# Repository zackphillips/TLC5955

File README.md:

# Arduino Library for the TLC5955 LED controller
This library is designed to work with the TLC5955 LED controller chip from Texas Instruments.
It can also be configured to work with many other LED driver chips from the TLC59** family
using the #define values in the header file. Tested on the Teensy 3.2. The library currently calls Teensy-specific
APIs (`SPI.setMOSI`, `analogWriteFrequency`, `analogWriteResolution`), so other boards need those calls ported.
It supports all features of the TLC5955 datasheet such as:
- Per-LED color control and dimming (16-bit)
- Per-LED white-balance
- Support for many, many LEDs by daisy-chaining TLC5955 chips in hardware (up to 255, configurable by the `chip_count` static variable)
- Per color-channel current controller
- PWM spread spectrum (ESPWM flag)
- Optional total-current limit (`enforce_max_current` / `max_current_amps`), estimated from GS, DC, BC and MC per datasheet Equation 1 (`get_total_current()`)

# Installation
After downloading the [Arduino IDE](http://www.arduino.cc/), open `examples/TLC5955/TLC5955.ino` for an example of how to implement this class in your own sketch. Please note that static variables (`chip_count`, `max_current_amps`, `enforce_max_current`, and the `_dc_data`, `_rgb_order`, `_grayscale_data` arrays) must be defined in your sketch so the buffers are sized at compile time.

## Grayscale Clock (GSCLK)
This library works best with a LED clock pulse with a frequency of 1MHz or higher. Most micro-controllers can achieve this, but implementations may be different. For the Teensy, the built-in command ```analogWriteFrequency``` can reliably set the output frequency of a PIN. For other boards, a simple google search should show you which registers to set.

# Stability
This library is stable and well-tested using a Teensy 3.2, but may have bugs for other boards. Please file issues on Github if you find a bug. The API may change slightly as new features are added.

# Contributing
Contributions are encouraged! Please create a pull request on Github, file an issue, or send me a message on Github.

# License
BSD

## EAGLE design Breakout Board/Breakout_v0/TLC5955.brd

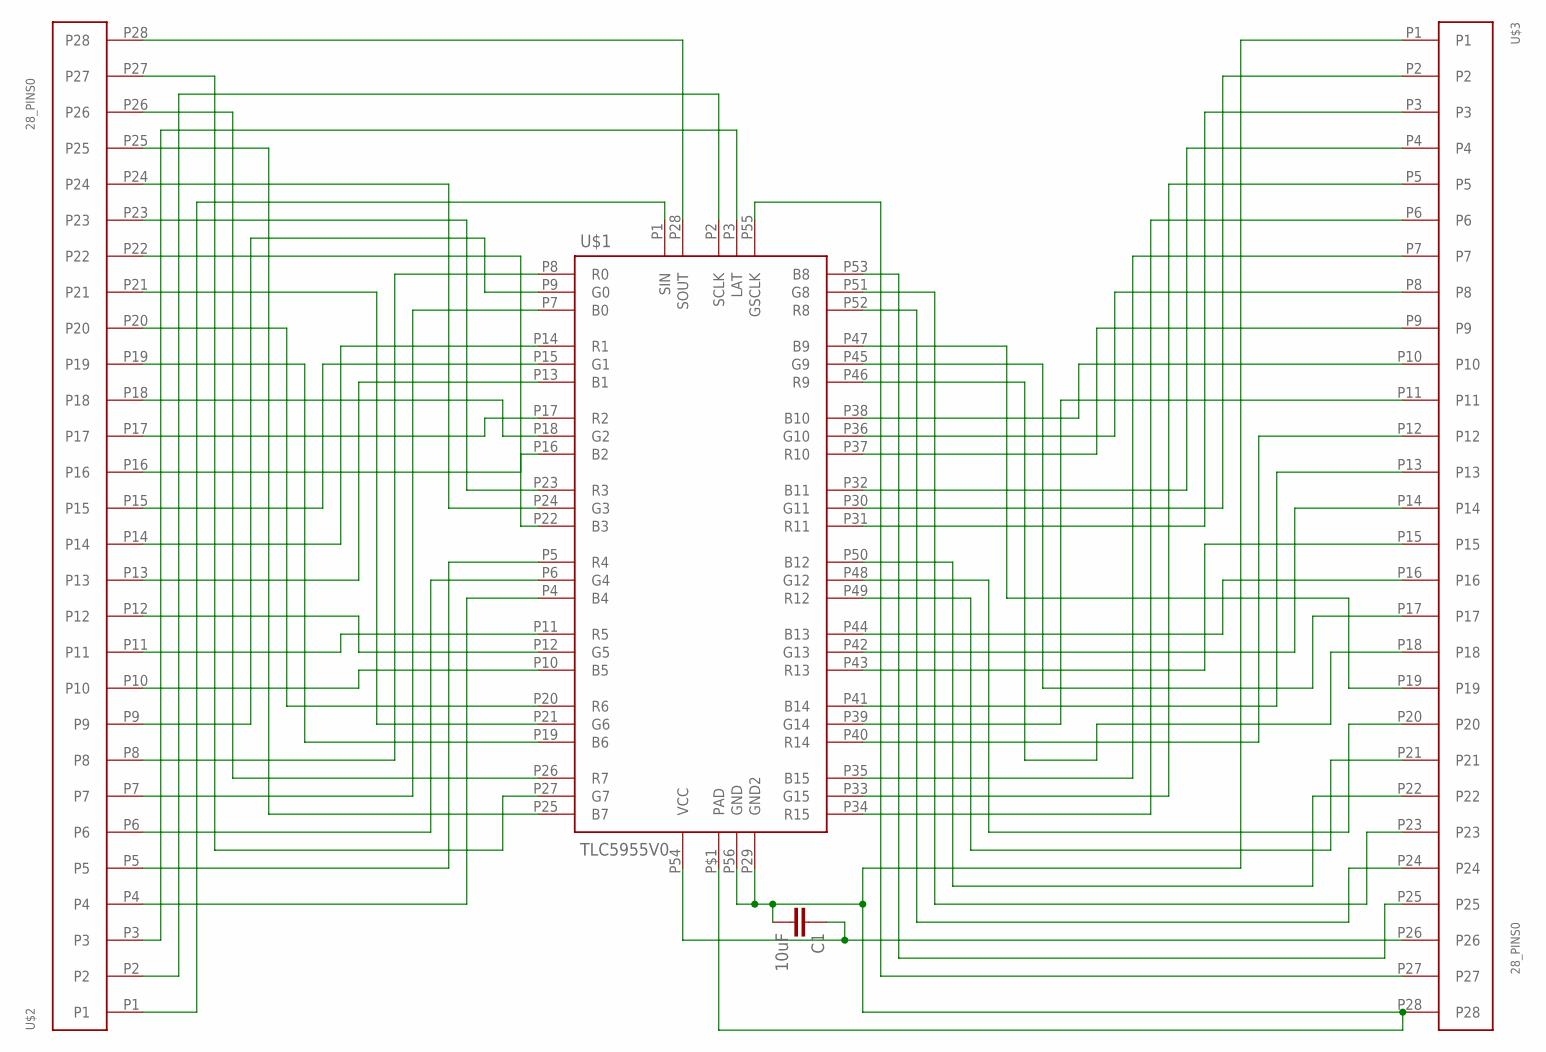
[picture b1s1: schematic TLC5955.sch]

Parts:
C1: 10uF; 0603-CAP
U$1: TLC5955V0; 56-HTSSOP
U$2, U$3: 28_PINS0; 28PIN_HOLES

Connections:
unnamed: U$1.P4 (B4), U$2.P4
unnamed: U$1.P5 (R4), U$2.P5
unnamed: U$1.P6 (G4), U$2.P6
unnamed: U$1.P7 (B0), U$2.P7
unnamed: U$1.P8 (R0), U$2.P8
unnamed: U$1.P21 (G6), U$2.P21
unnamed: U$1.P10 (B5), U$2.P10
unnamed: U$1.P11 (R5), U$2.P11
unnamed: U$1.P12 (G5), U$2.P12
unnamed: U$1.P13 (B1), U$2.P13
unnamed: U$1.P14 (R1), U$2.P14
unnamed: U$1.P15 (G1), U$2.P15
unnamed: U$1.P16 (B2), U$2.P16
unnamed: U$1.P17 (R2), U$2.P17
unnamed: U$1.P18 (G2), U$2.P18
unnamed: U$1.P19 (B6), U$2.P19
unnamed: U$1.P20 (R6), U$2.P20
unnamed: U$1.P22 (B3), U$2.P22
unnamed: U$1.P23 (R3), U$2.P23
unnamed: U$1.P24 (G3), U$2.P24
unnamed: U$1.P9 (G0), U$2.P9
unnamed: U$1.P25 (B7), U$2.P25
unnamed: U$1.P26 (R7), U$2.P26
unnamed: U$1.P28 (SOUT), U$2.P28
unnamed: U$1.P27 (G7), U$2.P27
unnamed: U$1.P1 (SIN), U$2.P1
unnamed: U$1.P2 (SCLK), U$2.P2
unnamed: U$1.P3 (LAT), U$2.P3
unnamed: U$1.P47 (B9), U$3.P19
unnamed: C1.1, U$1.P54 (VCC), U$3.P26
unnamed: U$1.P30 (G11), U$3.P2
unnamed: U$1.P31 (R11), U$3.P3
unnamed: U$1.P32 (B11), U$3.P4
unnamed: U$1.P33 (G15), U$3.P5
unnamed: U$1.P34 (R15), U$3.P6
unnamed: U$1.P35 (B15), U$3.P7
unnamed: U$1.P36 (G10), U$3.P8
unnamed: U$1.P37 (R10), U$3.P9
unnamed: U$1.P38 (B10), U$3.P10
unnamed: U$1.P39 (G14), U$3.P11
unnamed: U$1.P40 (R14), U$3.P12
unnamed: U$1.P41 (B14), U$3.P13
unnamed: U$1.P42 (G13), U$3.P14
unnamed: U$1.P43 (R13), U$3.P15
unnamed: U$1.P44 (B13), U$3.P16
unnamed: U$1.P45 (G9), U$3.P17
unnamed: U$1.P46 (R9), U$3.P18
unnamed: U$1.P48 (G12), U$3.P20
unnamed: U$1.P49 (R12), U$3.P21
unnamed: U$1.P50 (B12), U$3.P22
unnamed: U$1.P51 (G8), U$3.P23
unnamed: U$1.P52 (R8), U$3.P24
unnamed: U$1.P53 (B8), U$3.P25
unnamed: U$1.P55 (GSCLK), U$3.P27
unnamed: C1.2, U$1.P29 (GND2), U$1.P56 (GND), U$1.P$1 (PAD), U$3.P1, U$3.P28

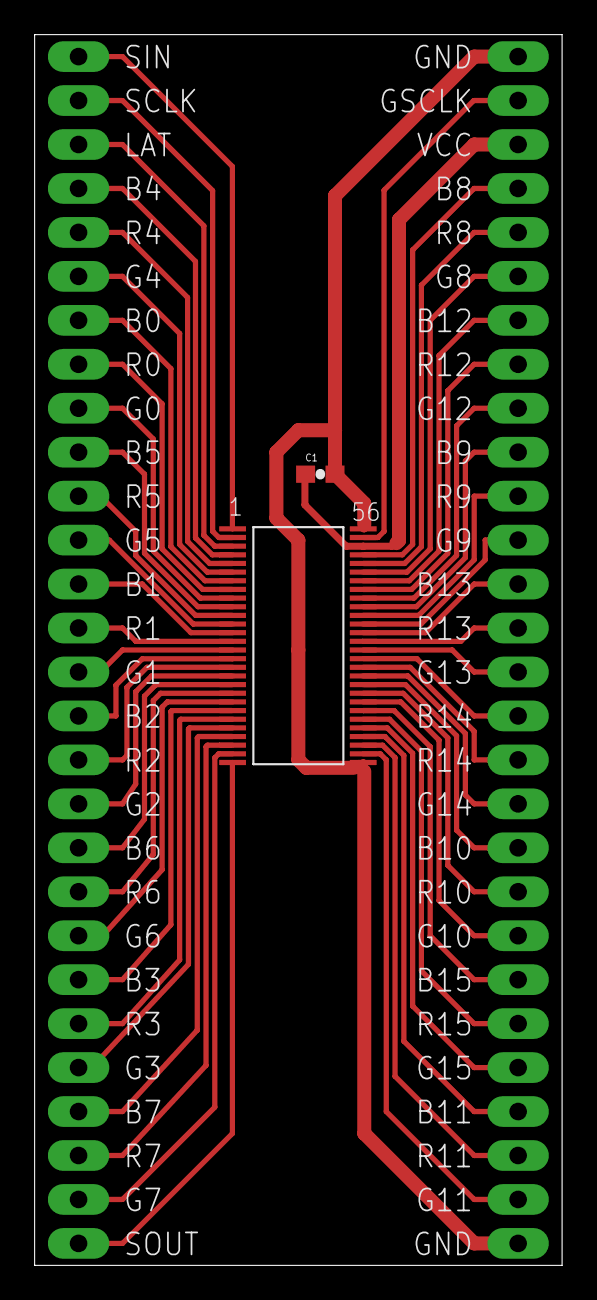
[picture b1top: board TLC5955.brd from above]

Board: 2 copper layers, 30.5 x 71.1 mm, 4 parts (0 on the bottom side), 55 nets.

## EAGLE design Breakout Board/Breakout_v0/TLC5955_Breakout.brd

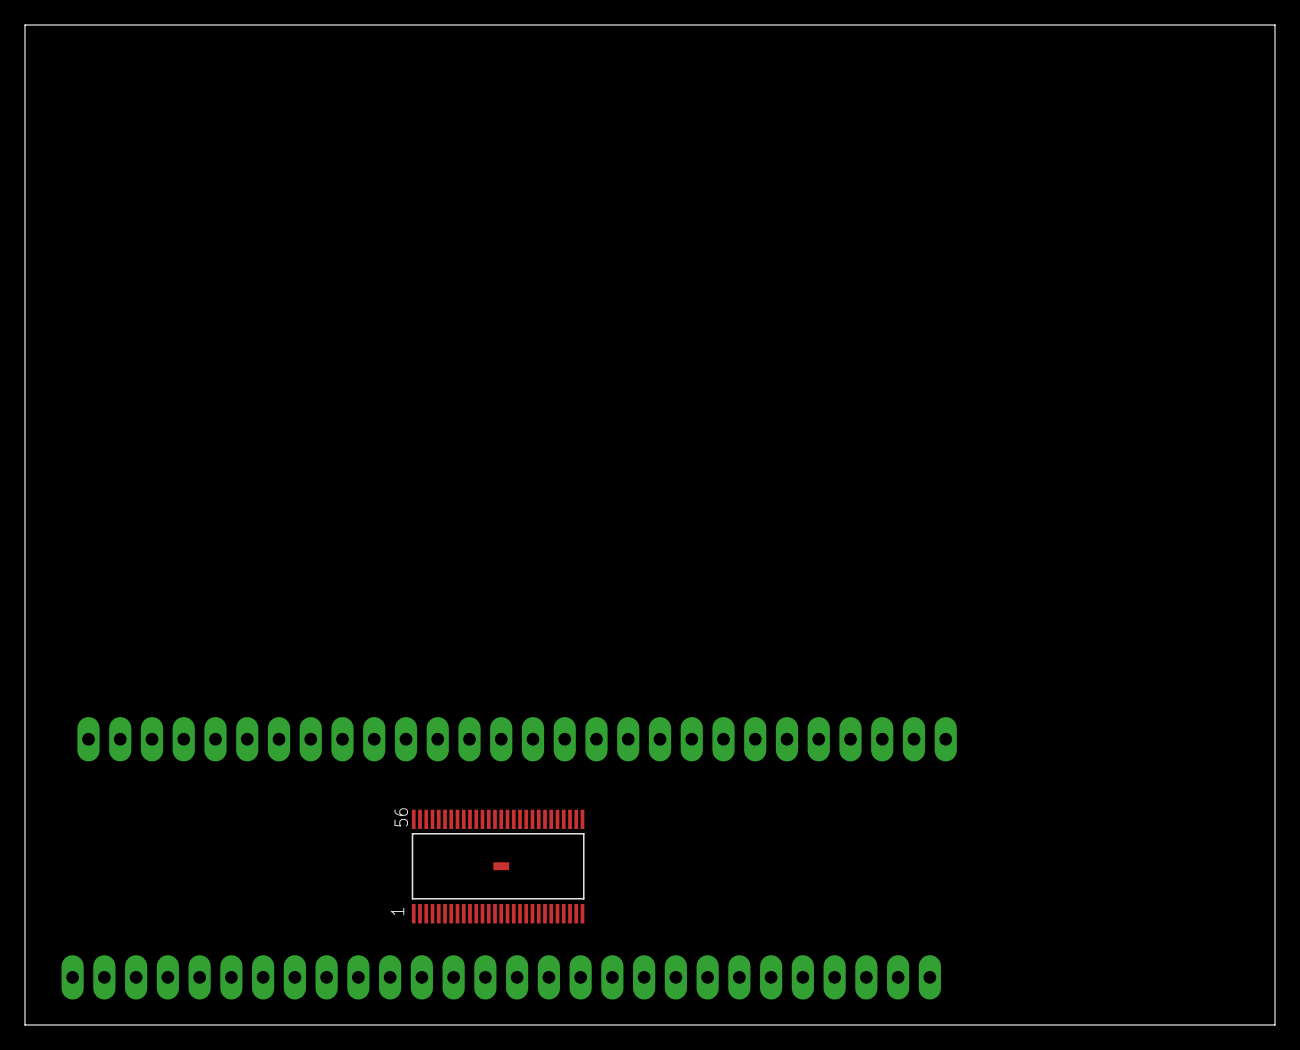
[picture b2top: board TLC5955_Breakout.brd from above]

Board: 2 copper layers, 100.0 x 80.0 mm, 3 parts (0 on the bottom side), 5 nets, no tracks yet.

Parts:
U$1: TLC5955V0; 56-HTSSOP
U$2, U$3: 28_PINS0; 28PIN_HOLES

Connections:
unnamed: U$1.P55, U$3.P2
unnamed: U$1.P54, U$3.P3
unnamed: U$1.P56, U$3.P1
unnamed: U$1.P53, U$3.P4
unnamed: U$1.P52, U$3.P6

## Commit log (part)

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2015-11-04 Initial commit - works well in my tests
2015-11-11 Fixed Latch Flickering Issue
2015-11-13 Fixed SPI Errors, Added SERIAL_DEBUG flag
2015-11-16 Many Serial Fixes, Working Version
    Up-to-date working version, currently configured to work with the
    Arduino MEGA
2015-11-16 Updated README files
2015-11-17 Fixed Bug when causing chained TLC chips to behave incorrectly
2015-12-03 Misc Cleanups
2015-12-03 Updated Breakout to correct version, added library
2015-12-10 Added Second Write to updateControl()
2015-12-11 Added ability to set rgb pin order, added setLED append method which doesn't overwrite existing led values
2016-02-25 Fixed Error in Example Program
2017-03-08 Added RGB Pin order setting
2017-03-08 added ability to read led positions
2017-06-05 Fixed Example
2017-08-28 Added ability to read from leds
2017-08-28 Removed dropbox.attr file (not sure how it got added)
2017-08-28 Removed and replaced a few more .icloud files
2018-01-23 minor bug fixes
2018-02-14 Cleaned up code to match var_name format, bug fixes to getChannel
2018-02-20 moved a lot of pre-compiler directives to class variables
2018-03-07 moved back to constant array sizes temporarily
2018-03-07 Moved tlc_count to static variable
2018-03-30 fixed bug in drawChannel
2018-04-03 added max current calculation and enforcement
2018-04-03 bug fixes to current checking
2018-04-05 clean-up
2018-04-22 Added example sketch and improved Readme.md
2018-04-22 removed superfulous examples
2018-06-18 Move example sketch to appropriately named folder
    This change causes the example sketch to be accessible via the Arduino IDE's File > Examples > TLC5955 menu after the library is installed.
    Reference:
    https://github.com/arduino/Arduino/wiki/Arduino-IDE-1.5:-Library-specification#library-examples
2018-10-19 Fixed small printing bug
2019-02-20 Added ability to set baud rate and gsclk frequency after initialization, cleaned up initialization in general.
2020-07-05 disable hte GSCLK when no LEDs are on
2020-07-05 simplify the patch
2020-10-18 Correctly set the SPI settings
2020-12-23 Revert "Correctly set the SPI settings"
    This reverts commit 6997cbab49501c700c152cb15cf43deef5247208.
2020-12-31 Fix management of SPI settings
2021-12-02 large refactor
2022-02-17 Disable gsclk during serial update
2022-12-20 added flush
2023-01-26 updated the way gsclock freq is set
2023-03-09 fix: properly revert gsclk
2024-05-01 added clear
2024-09-28 removed gsclk disable
2025-02-15 tested
2025-02-17 added ERROR
